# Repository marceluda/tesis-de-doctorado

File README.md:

# Material complementario de la Tesis de Doctorado de Marcelo Luda

En este sitio se publicará el material complementario. Se incluyen Scripts de programación, fuentes de los dibujos, etc.

## Trabajo de Tesis

El trabajo de tesis se puede acceder mediante la [biblioteca digital](https://bibliotecadigital.exactas.uba.ar/) de la [Facultad de Ciencias Exactas y Naturales de la UBA](https://exactas.uba.ar/):

  * Registro: https://bibliotecadigital.exactas.uba.ar/collection/tesis/document/tesis_n7160_Luda
  * [BAJAR PDF](https://bibliotecadigital.exactas.uba.ar/download/tesis/tesis_n7160_Luda.pdf)

## Material disponible en este repositorio

 - [Capítulo 6: Estructura atómica del Rubidio](https://github.com/marceluda/tesis-de-doctorado/tree/main/cap06)
 - [Capítulo 7: Modelo de espectroscopía de absorción](https://github.com/marceluda/tesis-de-doctorado/tree/main/cap07)
 - [Capítulo 8: Modelo de atrapamiento coherente de población (CPT)](https://github.com/marceluda/tesis-de-doctorado/tree/main/cap08)
 - [Capítulo 9: Espectroscopía de absorción de gas de Rb usando un microcontrolador Arduino](https://github.com/marceluda/tesis-de-doctorado/tree/main/cap09)
 - [Capítulo 15: Estabilización de λ a Fabry-Perot mediante PDH](https://github.com/marceluda/tesis-de-doctorado/tree/main/cap15)
 - [Capítulo 18: Espectro de absorción y control de λ](https://github.com/marceluda/tesis-de-doctorado/tree/main/cap18)
 - [Capítulo 19: Espectro de CPT y control de RF](https://github.com/marceluda/tesis-de-doctorado/tree/main/cap19)

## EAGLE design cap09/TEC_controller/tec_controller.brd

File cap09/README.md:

# Capítulo 9: Espectroscopía de absorción de gas de Rb usando un microcontrolador Arduino

Se montó un sistema de actuadores para controlar un ECDL y realizar un experimento de espectroscopía de absorción saturada, como en este esquema:

Se implementó un algoritmo de estabilización a un pozo de transmitancia, adquiriendo porciones del espectro en el entorno de longitud de onda del láser, realizando un ajuste lineal y corrigiendo la en función del valor de la pendiente. Aquí se puede ver una animación del programa en funcionamiento:

Para ello se debió controlar:
  - Corriente del láser
  - Temperatura del láser
  - Posición de la red de difracción, emdiante una tensión en un PZT

Se desarrollaron circuitos controladores para cada una de estas variables físicas. También se desarrolló un sistema de instrumentación basado en Arduino que funcionó como un comando central de operación.

## Controladores

### Controlador de PZT

Simplemente es un circuito de adaptación para el integrado [E-661.OE](hojas_de_datos/e-660_userpz45e223.pdf). Tiene un canal de control de off-set y otro de barrido.
El de off-set puede ser controlado por una entrada PWM  o mediante un potenciómetro multivuelta.
El de barrido por una entrada BNC o por otro PWM. Los canale se configuran mediante dos jumpres.

-------

<p align="center">
<strong>
<a href="DriverPZT">Driver PZT</a>
</strong>
</p>

-------

### Controlador de Corriente

Es un circuito de adaptación de tensiones para controlar el integrado [FL500](hojas_de_datos/fl500.pdf), que es una fuente de corriente de hasta 500 mA.
Tiene un control de off-set t un control de barrido, que incluye atenuación variable y la posibilidad de invertir la dirección de barrido respecto a la señal de control de entrada.

-------

<p align="center">
<strong>
<a href="DriverFL500">Driver Corriente</a>
</strong>
</p>

-------

### Controlador de Temperatura

Es un circuito de realimentación negativa con un controlador PID para estabilizar la temperatura del láser. Actúa sobre una celda Peltier y sensa un terminstor, que es comparado con una tensión de referencia.

-------

<p align="center">
<strong>
<a href="TEC_controller">Driver TEC</a>
</strong>
</p>

-------

## Controlador central basado en Arduino

Es un *shield* para [Arduino MEGA 2560](https://store.arduino.cc/usa/mega-2560-r3) que permite incorporarle:

  * Generador de barridos triangulares que incluye:
    * Control de frecuencia
    * Control de amplitud de barrido
    * Control de off-set
  * ADC con amplificación y offset
  * DACs a base de PWM y pasabajos

### Diseño de circuito

-------

<p align="center">
<strong>
<a href="shield-control">Arduino Shield-Control</a>
</strong>
</p>

-------

### Centro de comandos

Se programó el dispositivo para correr un [centro de comandos](command_center) con comunicación serie para controlar el comportamiento del controlador, configurar parámetros y adquirir datos.

```graphql
# Los comandos se componen de la siguiente estructura:
# (comando)( )(param1)[ ][param2]
# donde () implica obligatorio, [] opcional y ( ) es un white_space

# debug modes
# 0   --> nada de debug
# >=5 --> info irrelevante

Comandos

get -----> P(2-13)  ---> Trae ultimo valor seteado al pin Px
      |--> D(24-29) ---> Lee valor digital del pin Dx
      |--> D(30-39) ---> Trae ultimo valor seteado al pin Dx
      |--> A(0-4)   ---> Lee valor analogico del pin Ax (pin x+54)

set -----> P(2-13) (0-255) ---> Setea el PWM Px en un valor 0-255
      |--> D(30-39) (0-1)  ---> Setea el pin digital Dx en un valor 0-1

debug ---> (num)          ---> Setea el modo de debugging en el valor "num"

trig ---> (off||up||down) ---> Habilita el trigger en el pin 19 para subida, bajada, o lo apaga

binary --> (num)          ---> Si num>0 habilita el modo binario. Sino, lo deshabilita.

vref ---> (num)   ---> Cambia la tensión de referencia del ADC
                          |--> num=1  ---> Vref=1.1V
                          |--> num=2  ---> Vref=2.56V
                          |--> num=9  ---> Vref externo
                          |--> cualquier otro ---> Vref=Vcc~5V (DEFAULT)

curv  ----> A(0-4)   ---> Levanta NN puntos del pin Ax

curv2 ----> A(0-4) ----> D(19-20||30-39)   ---> Levanta NN puntos del pin Ax y otra de NN puntos del pin Dx

# En modo binario las respuestas son:

--> 0 EOT                    ---> Comando recibido
--> 1 EOT Val EOT            ---> Envio de un integer binario
--> 2 EOT Num EOT Vals EOT   ---> Envio de Num integers binarios
--> 9 EOT msg EOT            ---> Envio de un texto informativo

```

<details>
<summary>Ejemplo de comando remoto en Matlab</summary>

```MATLAB

%s=serial('/dev/ttyACM1');
s=serial('COM6');
set(s,'BaudRate',57600);
set(s,'InputBufferSize',4096);

% Nota: para que el MATLAB lea correctamente el puerto es necesario
%       crear un archivo en el home folder donde abre el matlab
%       que en mi caso es /home/lolo
%
%       Archivo: java.opts
%       -Dgnu.io.rxtx.SerialPorts=/dev/ttyS0:/dev/ttyS1:/dev/USB0:/dev/ttyACM0:/dev/ttyACM1
%

fopen(s)
pause(2)
leer(s)

cmd(s,'binary 1')
cmd(s,'trig up')
cmd(s,'trig down')
cmd(s,'trig off')

leer(s)

escribir(s,'\n')

for i=1:20
    plot(cmd(s,'curv A0')*5/1024,'.-')
    pause(0.1)
end

escala=1024

cmd(s,'ate 15')
cmd(s,'set P9 115')

[yy,tt]=curvA0(s);
plot(tt,yy,'.-')
plot(tt,smooth(yy),'.-')

cmd(s,'vref 9')
cmd(s,'delay 250 u')

cmd(s,'set P10 150')
cmd(s,'set P10 0')
cmd(s,'set P9 100')

cmd(s,'set D30 0')
cmd(s,'set D32 0')
cmd(s,'set D34 0')
cmd(s,'set D36 1')

cmd(s,'vref 5')
cmd(s,'vref 1')

tic()
cmd(s,'curv2 A0 D26')
toc()

fclose(s)
```

</details>

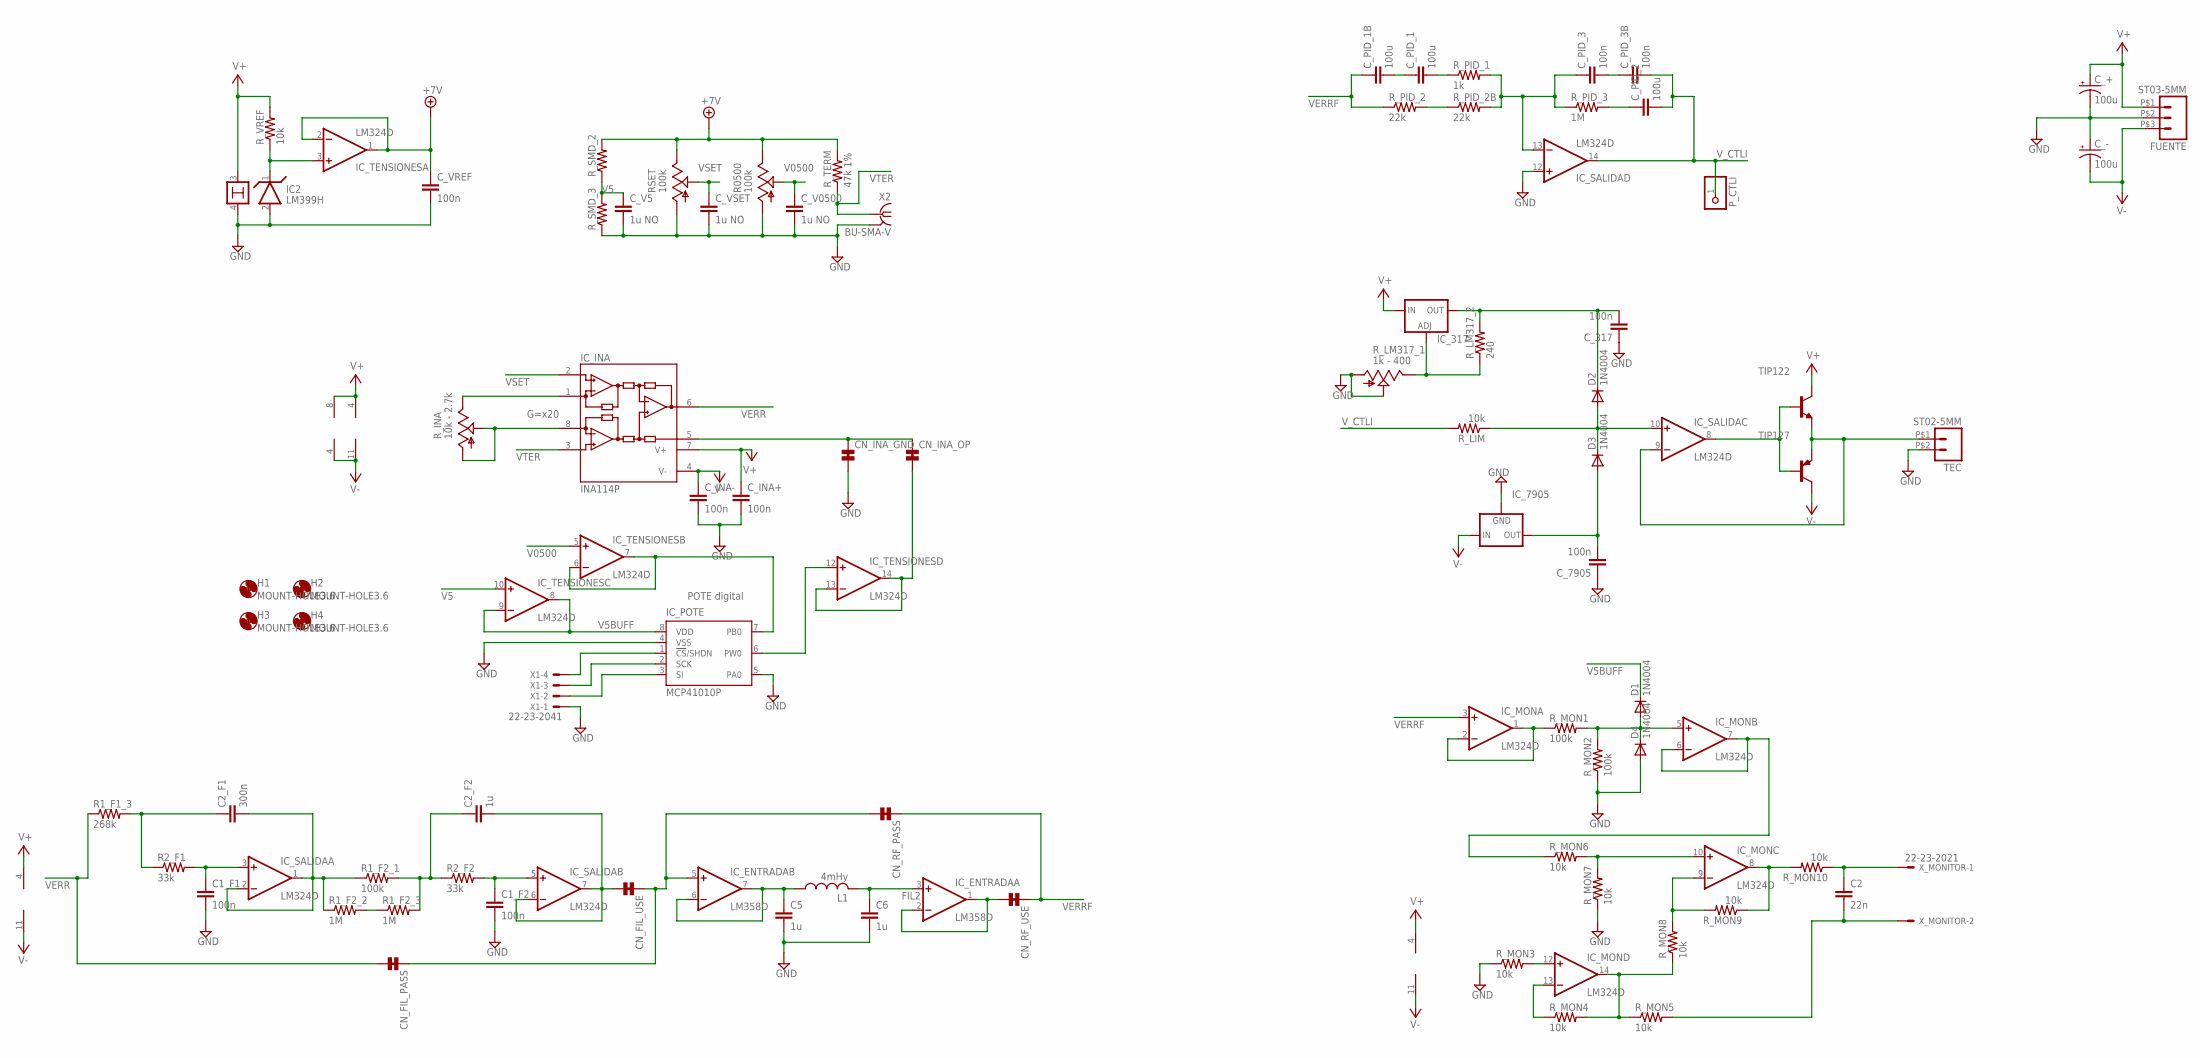
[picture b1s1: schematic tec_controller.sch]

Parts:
C1_F1, C1_F2: 100n; C0603
C2: 22n; C1206
C2_F1: 300n; C0603
C2_F2, C5, C6: 1u; C0805
CN_FIL_PASS: LINK; LINK_PAC_0603
CN_FIL_USE: LINK; LINK_PAC_0603
CN_INA_GND: LINK; LINK_PAC_0603
CN_INA_OP: LINK; LINK_PAC_0603
CN_RF_PASS: LINK; LINK_PAC_0603
CN_RF_USE: LINK; LINK_PAC_0603
C_317, C_7905: 100n; C0603
C_+: 100u; E3,5-10
C_-: 100u; E3,5-10
C_INA+: 100n; C0603
C_INA-: 100n; C0603
C_PID_1, C_PID_1B, C_PID_2: 100u; C050-050X075
C_PID_3, C_PID_3B: 100n; C0603
C_V5, C_V0500: 1u NO; C0805
C_VREF: 100n; C0603
C_VSET: 1u NO; C0805
D1, D2, D3, D4: 1N4004; DO41-10
FUENTE: ST03-5MM; EK500V-03P
H1, H2, H3, H4: MOUNT-HOLE3.6; 3,6
IC2: LM399H; TO39/4
IC_317: LM317TS; 317TS
IC_7905: 79XXS
IC_ENTRADA: LM358D; SO08
IC_INA: INA114P; DIL08
IC_MON: LM324D; SO14
IC_POTE: MCP41010P; DIL8
IC_SALIDA: LM324D; SO14
IC_TENSIONES: LM324D; SO14
L1: 4mHy; 0207/15
P_CTLI: PINHD-1X1; 1X01
R1_F1_3: 268k; 0207/15
R1_F2_1: 100k; M1206
R1_F2_2, R1_F2_3: 1M; M1206
R2_F1, R2_F2: 33k; M1206
R0500: 100k; B64Y
RSET: 100k; B64Y
R_INA: 10k - 2.7k; B64Y
R_LIM: 10k; M1206
R_LM317_1: 1k - 400; B64Y
R_LM317_2: 240; 0207/10
R_MON1, R_MON2: 100k; M1206
R_MON3, R_MON4, R_MON5, R_MON6, R_MON7, R_MON8, R_MON9, R_MON10: 10k; M1206
R_PID_1: 1k; M1206
R_PID_2, R_PID_2B: 22k; M1206
R_PID_3: 1M; M1206
R_SMD_2, R_SMD_3: R-US_M1206; M1206
R_TERM: 47k 1%; 0207/10
R_VREF: 10k; M1206
TEC: ST02-5MM; EK500V-02P
TIP122: -NPN-TO126V; TO126V
TIP127: -PNP-TO126V; TO126V
X1: 22-23-2041
X2: BU-SMA-V
X_MONITOR: 22-23-2021

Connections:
+7V: C_VREF.1, IC_TENSIONES.1 (OUT), IC_TENSIONES.2 (-IN), R0500.E, RSET.E, R_SMD_2.2, R_TERM.2
FIL2: C6.1, IC_ENTRADA.3 (+IN), L1.2
GND: C1_F1.2, C1_F2.2, C5.2, C6.2, CN_INA_GND.2, C_317.1, C_7905.1, C_+.-, C_-.+, C_INA+.2, C_INA-.2, C_V5.2, C_V0500.2, C_VREF.2, C_VSET.2, D4.A, FUENTE.P$2 (2), IC2.2, IC2.4, IC_7905.GND, IC_POTE.4 (VSS), IC_POTE.5 (PA0), IC_SALIDA.12 (+IN), R0500.A, RSET.A, R_LM317_1.A, R_LM317_1.S, R_MON2.1, R_MON3.1, R_MON7.1, R_SMD_3.1, TEC.P$2 (2), X1.1, X2.2, X2.3 (2), X2.4 (2), X2.5 (2)
unnamed: IC2.1, IC_TENSIONES.3 (+IN), R_VREF.1
unnamed: IC_INA.1 (RG), R_INA.E
unnamed: IC_INA.8 (RG), R_INA.A, R_INA.S
unnamed: C_PID_1.2, R_PID_1.1
unnamed: IC_MON.1 (OUT), IC_MON.2 (-IN), R_MON1.1
unnamed: IC_MON.12 (+IN), R_MON3.2
unnamed: C5.1, IC_ENTRADA.6 (-IN), IC_ENTRADA.7 (OUT), L1.1
unnamed: CN_RF_USE.2, IC_ENTRADA.1 (OUT), IC_ENTRADA.2 (-IN)
unnamed: C2_F1.1, R1_F1_3.2, R2_F1.1
unnamed: C1_F1.1, IC_SALIDA.3 (+IN), R2_F1.2
unnamed: C2_F1.2, IC_SALIDA.1 (OUT), IC_SALIDA.2 (-IN), R1_F2_1.1, R1_F2_2.1
unnamed: R1_F2_2.2, R1_F2_3.1
unnamed: C2_F2.1, R1_F2_1.2, R1_F2_3.2, R2_F2.1
unnamed: IC_POTE.7 (PB0), IC_TENSIONES.6 (-IN), IC_TENSIONES.7 (OUT)
unnamed: C1_F2.1, IC_SALIDA.5 (+IN), R2_F2.2
unnamed: IC_POTE.6 (PW0), IC_TENSIONES.12 (+IN)
unnamed: CN_INA_GND.1, CN_INA_OP.1, IC_INA.5 (REF)
unnamed: IC_POTE.1 (!CS!/SHDN), X1.4
unnamed: CN_INA_OP.2, IC_TENSIONES.13 (-IN), IC_TENSIONES.14 (OUT)
unnamed: IC_POTE.2 (SCK), X1.3
unnamed: IC_POTE.3 (SI), X1.2
unnamed: R_PID_2.2, R_PID_2B.1
unnamed: C_PID_1.1, C_PID_1B.2
unnamed: C_PID_3.1, IC_SALIDA.13 (-IN), R_PID_1.2, R_PID_2B.2, R_PID_3.1
unnamed: IC_317.1 (ADJ), R_LM317_1.E, R_LM317_2.1
unnamed: C_PID_2.1, R_PID_3.2
unnamed: D2.A, D3.C, IC_SALIDA.10 (+IN), R_LIM.1
unnamed: C_PID_3.2, C_PID_3B.1
unnamed: IC_SALIDA.8 (OUT), TIP122.3 (B), TIP127.3 (B)
unnamed: D1.A, D4.C, IC_MON.5 (+IN), R_MON1.2, R_MON2.2
unnamed: IC_MON.6 (-IN), IC_MON.7 (OUT), R_MON6.1
unnamed: IC_MON.10 (+IN), R_MON6.2, R_MON7.2
unnamed: IC_MON.9 (-IN), R_MON8.2, R_MON9.2
unnamed: IC_MON.14 (OUT), R_MON4.2, R_MON5.1, R_MON8.1
unnamed: IC_MON.13 (-IN), R_MON4.1
unnamed: C2.2, R_MON5.2, X_MONITOR.2
unnamed: IC_MON.8 (OUT), R_MON9.1, R_MON10.2
unnamed: C2.1, R_MON10.1, X_MONITOR.1
V5: C_V5.1, IC_TENSIONES.10 (+IN), R_SMD_2.1, R_SMD_3.2
V5BUFF: D1.C, IC_POTE.8 (VDD), IC_TENSIONES.8 (OUT), IC_TENSIONES.9 (-IN)
V0500: C_V0500.1, IC_TENSIONES.5 (+IN), R0500.S
V+: C_+.+, C_INA+.1, FUENTE.P$1 (1), IC2.3, IC_317.3 (IN), IC_ENTRADA.8 (V+), IC_INA.7 (V+), IC_MON.4 (V+), IC_SALIDA.4 (V+), IC_TENSIONES.4 (V+), R_VREF.2, TIP122.2 (C)
V-: C_-.-, C_INA-.1, FUENTE.P$3 (3), IC_7905.IN, IC_ENTRADA.4 (V-), IC_INA.4 (V-), IC_MON.11 (V-), IC_SALIDA.11 (V-), IC_TENSIONES.11 (V-), TIP127.2 (C)
VERR: CN_FIL_PASS.2, IC_INA.6 (OUT), R1_F1_3.1
VERRF: CN_RF_PASS.1, CN_RF_USE.1, C_PID_1B.1, IC_MON.3 (+IN), R_PID_2.1
VERRF_B: CN_FIL_PASS.1, CN_FIL_USE.1, CN_RF_PASS.2, IC_ENTRADA.5 (+IN)
VERRF_SALIDA: C2_F2.2, CN_FIL_USE.2, IC_SALIDA.6 (-IN), IC_SALIDA.7 (OUT)
VSET: C_VSET.1, IC_INA.2 (-IN), RSET.S
VTEC: IC_SALIDA.9 (-IN), TEC.P$1 (1), TIP122.1 (E), TIP127.1 (E)
VTER: IC_INA.3 (+IN), R_TERM.1, X2.1
V_317: C_317.2, D2.C, IC_317.2 (OUT), R_LM317_2.2
V_7905: C_7905.2, D3.A, IC_7905.OUT
V_CTLI: C_PID_2.2, C_PID_3B.2, IC_SALIDA.14 (OUT), P_CTLI.1, R_LIM.2

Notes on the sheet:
POTE digital
G=x20

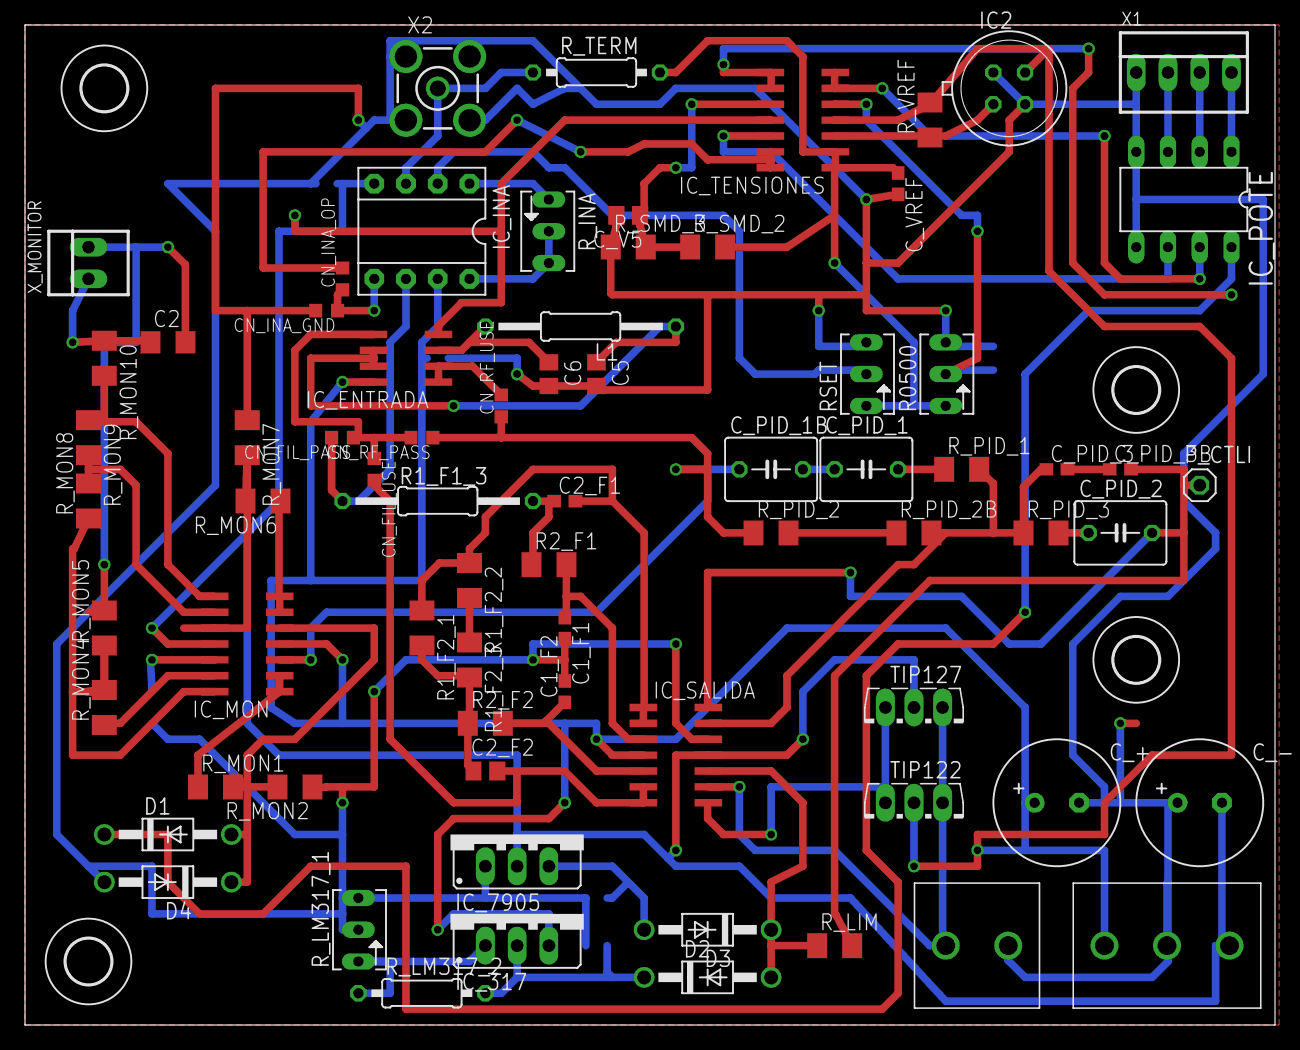
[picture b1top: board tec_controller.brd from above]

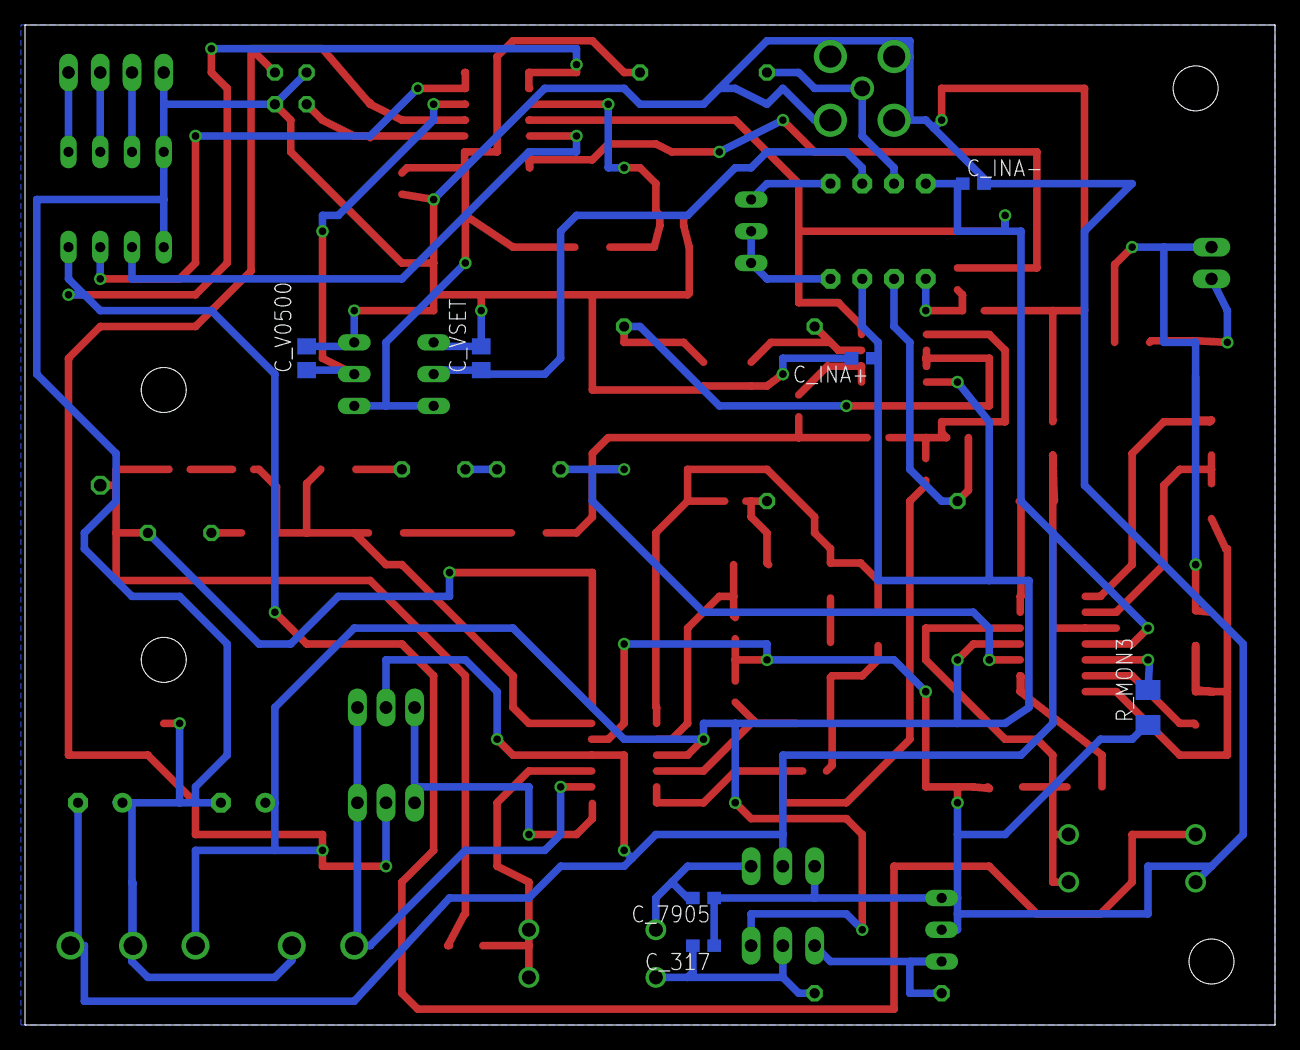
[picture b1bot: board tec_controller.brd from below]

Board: 2 copper layers, 100.0 x 80.0 mm, 84 parts (7 on the bottom side), 56 nets.

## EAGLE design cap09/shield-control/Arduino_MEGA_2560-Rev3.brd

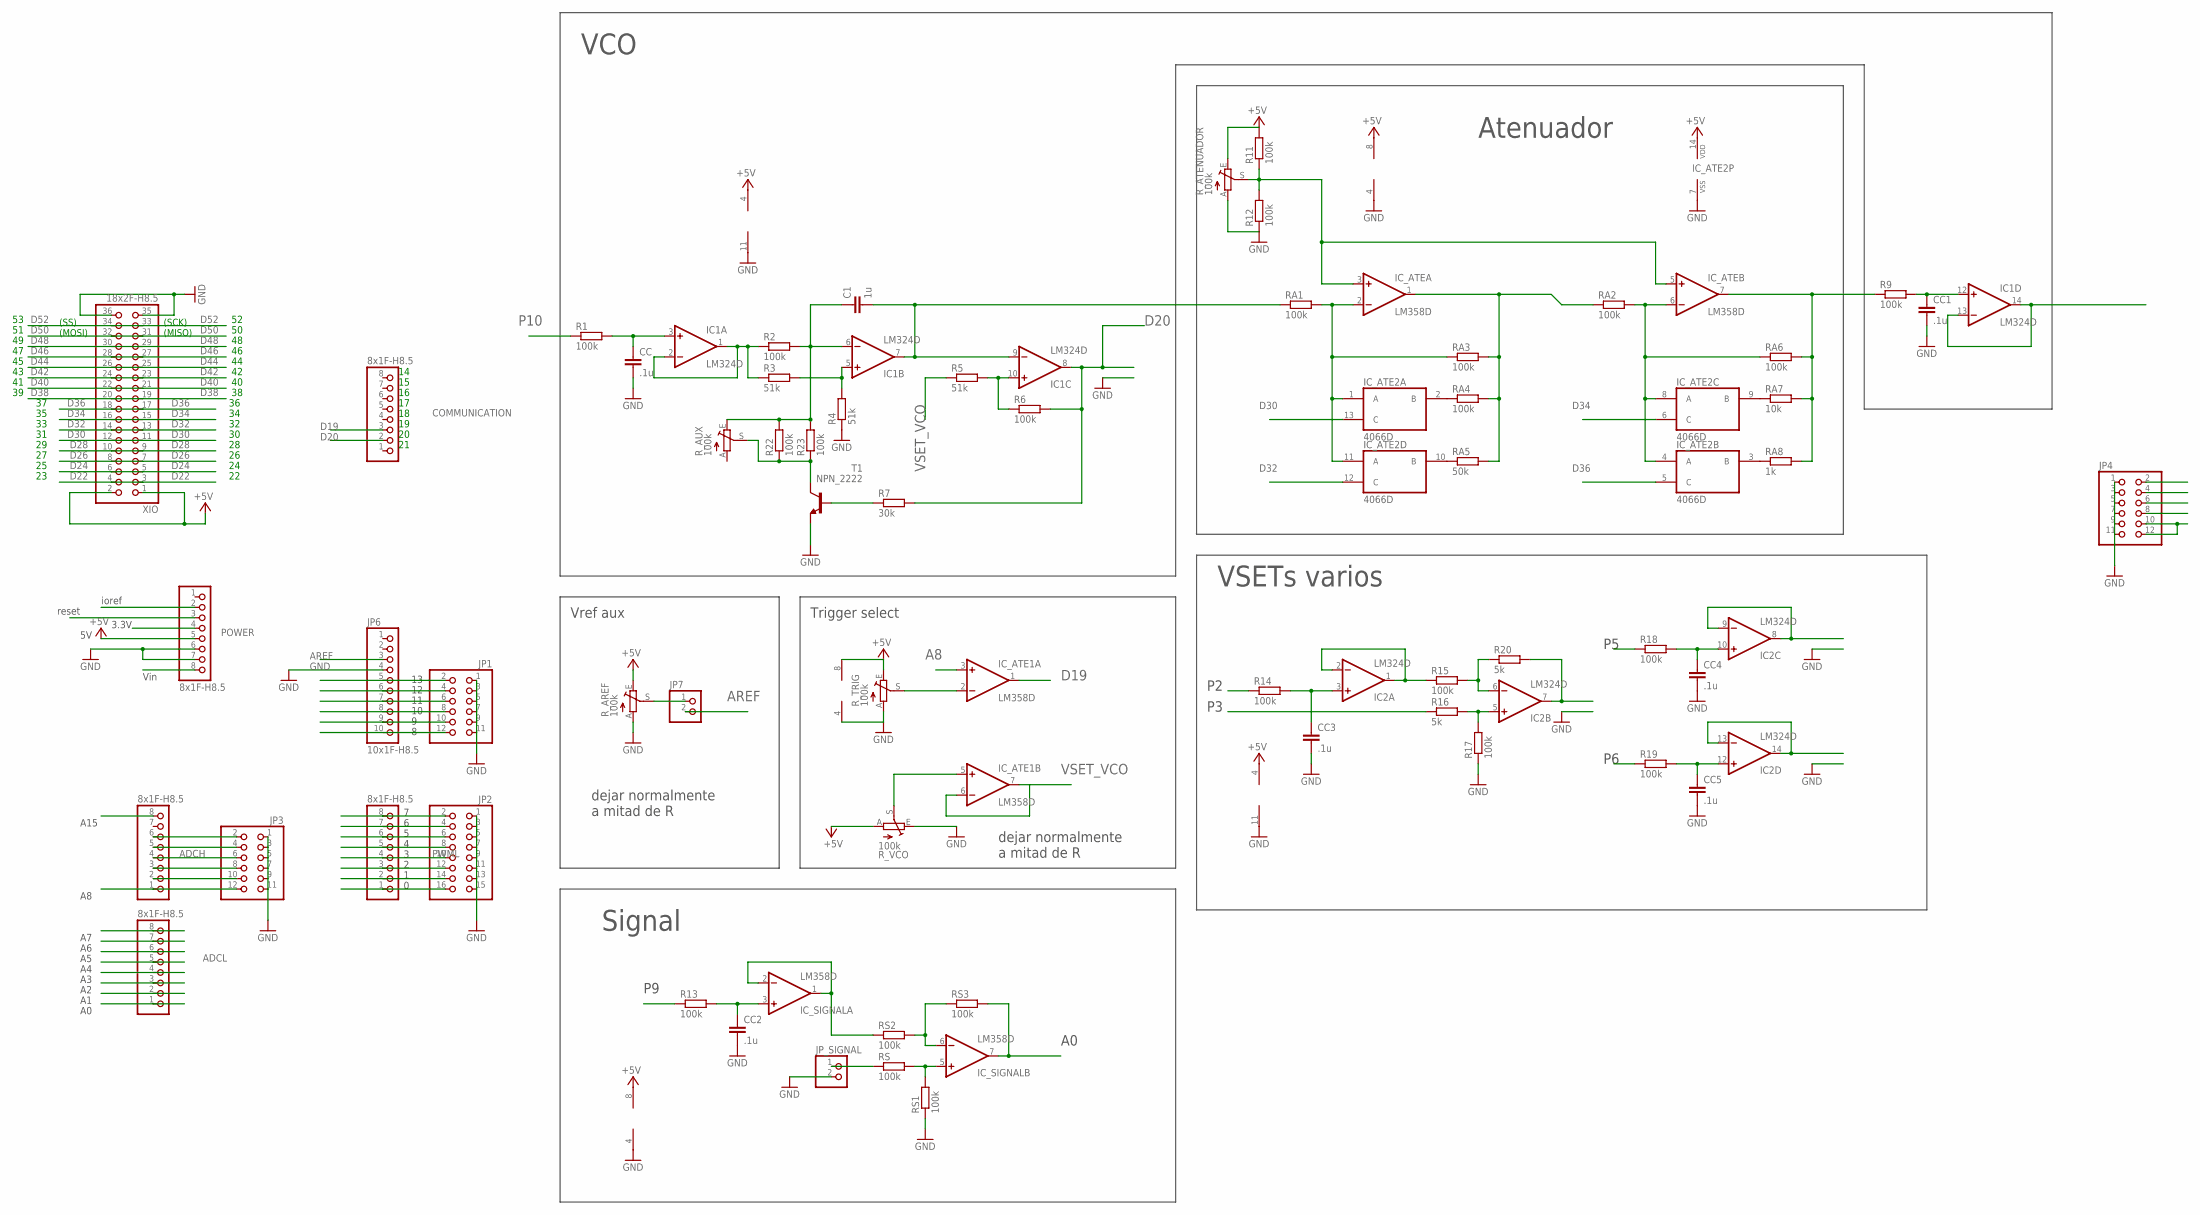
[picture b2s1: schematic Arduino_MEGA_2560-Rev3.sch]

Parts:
ADCH: 8x1F-H8.5; 1X08
ADCL: 8x1F-H8.5; 1X08
C1: 1u; C1812
CC, CC1, CC2, CC3, CC4, CC5: .1u; C1812
COMMUNICATION: 8x1F-H8.5; 1X08
IC1, IC2: LM324D; SO14
IC_ATE, IC_ATE1: LM358D; SO08
IC_ATE2: 4066D; SO14
IC_SIGNAL: LM358D; SO08
JP1, JP3, JP4: PINHD-2X6; 2X06
JP2: PINHD-2X8; 2X08
JP6: 10x1F-H8.5; 1X10
JP7: PINHD-1X2; 1X02
JP_SIGNAL: PINHD-1X2; 1X02
POWER: 8x1F-H8.5; 1X08
PWML: 8x1F-H8.5; 1X08
R1, R2, R6, R9, R11, R12, R13, R14, R15, R17, R18, R19, R22, R23: 100k; R1206
R3, R4, R5: 51k; R1206
R7: 30k; 0204/7
R16, R20: 5k; R1206
RA1, RA2, RA3, RA4, RA6: 100k; R1206
RA5: 50k; R1206
RA7: 10k; 0204/7
RA8: 1k; 0204/7
RS, RS1, RS2, RS3: 100k; R1206
R_AREF: 100k; B64Y
R_ATENUADOR: 100k; B64Y
R_AUX: 100k; B64Y
R_TRIG: 100k; B64Y
R_VCO: 100k; B64Y
T1: NPN_2222; TO19_SUP
XIO: 18x2F-H8.5; 2X18

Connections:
3V3: POWER.4
+5V: IC1.4 (V+), IC2.4 (V+), IC_ATE.8 (V+), IC_ATE1.8 (V+), IC_ATE2.14 (VDD), IC_SIGNAL.8 (V+), POWER.5, R11.2, R_AREF.E, R_ATENUADOR.E, R_TRIG.E, R_VCO.A, XIO.1, XIO.2
A0: ADCL.1, IC_SIGNAL.7 (OUT), RS3.2
A1: ADCL.2
A2: ADCL.3
A3: ADCL.4
A4: ADCL.5
A5: ADCL.6
A6: ADCL.7
A7: ADCL.8
A8: ADCH.1, IC_ATE1.3 (+IN), JP3.12
A9: ADCH.2, JP3.10
A9BIS: IC_ATE1.5 (+IN), R_VCO.S
A10: ADCH.3, JP3.8
A11: ADCH.4, JP3.6
A12: ADCH.5, JP3.4
A13: ADCH.6, JP3.2
A15: ADCH.8
AREF: JP6.3, JP7.2
D19: COMMUNICATION.3, IC_ATE1.1 (OUT)
D20: COMMUNICATION.2, IC1.8 (OUT), JP4.2, R6.2, R7.2
D22: XIO.3, XIO.4
D24: XIO.5, XIO.6
D26: XIO.7, XIO.8
D28: XIO.9, XIO.10
D30: IC_ATE2.13 (C), XIO.11, XIO.12
D32: IC_ATE2.12 (C), XIO.13, XIO.14
D34: IC_ATE2.6 (C), XIO.15, XIO.16
D36: IC_ATE2.5 (C), XIO.17, XIO.18
D38: XIO.19, XIO.20
D40: XIO.21, XIO.22
D42: XIO.23, XIO.24
D44: XIO.25, XIO.26
D46: XIO.27, XIO.28
D48: XIO.29, XIO.30
D50: XIO.31, XIO.32
D52: XIO.33, XIO.34
GND: CC.2, CC1.2, CC2.2, CC3.2, CC4.2, CC5.2, IC1.11 (V-), IC2.11 (V-), IC_ATE.4 (V-), IC_ATE1.4 (V-), IC_ATE2.7 (VSS), IC_SIGNAL.4 (V-), JP1.1, JP1.3, JP1.5, JP1.7, JP1.9, JP1.11, JP2.1, JP2.3, JP2.5, JP2.7, JP2.9, JP2.11, JP2.13, JP2.15, JP3.1, JP3.3, JP3.5, JP3.7, JP3.9, JP3.11, JP4.1, JP4.3, JP4.5, JP4.7, JP4.9, JP4.11, JP6.4, JP_SIGNAL.2, POWER.6, POWER.7, R4.1, R12.1, R17.1, RS1.1, R_AREF.A, R_ATENUADOR.A, R_TRIG.A, R_VCO.E, T1.3 (E), XIO.35, XIO.36
unnamed: IC_ATE1.2 (-IN), R_TRIG.S
unnamed: CC.1, IC1.3 (+IN), R1.2
unnamed: IC1.1 (OUT), IC1.2 (-IN), R2.1, R3.1
unnamed: IC_ATE.2 (-IN), IC_ATE2.1 (A), IC_ATE2.11 (A), RA1.2, RA3.1
unnamed: C1.1, IC1.6 (-IN), R2.2, R22.2, R23.2, R_AUX.E
unnamed: IC_ATE2.3 (B), RA8.1
unnamed: IC1.5 (+IN), R3.2, R4.2
unnamed: IC1.10 (+IN), R5.2, R6.1
unnamed: IC_ATE2.10 (B), RA5.1
unnamed: R7.1, T1.2 (B)
unnamed: CC1.1, IC1.12 (+IN), R9.2
unnamed: IC_SIGNAL.1 (OUT), IC_SIGNAL.2 (-IN), RS2.1
unnamed: IC_ATE.6 (-IN), IC_ATE2.4 (A), IC_ATE2.8 (A), RA2.2, RA6.1
unnamed: IC_ATE.1 (OUT), RA2.1, RA3.2, RA4.2, RA5.2
unnamed: IC_ATE2.2 (B), RA4.1
unnamed: IC_SIGNAL.5 (+IN), RS.2, RS1.2
unnamed: IC_SIGNAL.6 (-IN), RS2.2, RS3.1
unnamed: CC3.1, IC2.3 (+IN), R14.2
unnamed: IC_ATE2.9 (B), RA7.1
unnamed: IC2.1 (OUT), IC2.2 (-IN), R15.1
unnamed: CC2.1, IC_SIGNAL.3 (+IN), R13.2
unnamed: IC2.6 (-IN), R15.2, R20.1
unnamed: IC_ATE.7 (OUT), R9.1, RA6.2, RA7.2, RA8.2
unnamed: IC_ATE.3 (+IN), IC_ATE.5 (+IN), R11.1, R12.2, R_ATENUADOR.S
unnamed: IC2.5 (+IN), R16.2, R17.2
unnamed: CC5.1, IC2.12 (+IN), R19.2
unnamed: CC4.1, IC2.10 (+IN), R18.2
unnamed: R22.1, R23.1, R_AUX.S, T1.1 (C)
unnamed: JP7.1, R_AREF.S
P0: JP2.16, PWML.1
P1: JP2.14, PWML.2
P2: JP2.12, PWML.3, R14.1
P3: JP2.10, PWML.4, R16.1
P4: JP2.8, PWML.5
P5: JP2.6, PWML.6, R18.1
P6: JP2.4, PWML.7, R19.1
P7: JP2.2, PWML.8
P8: JP1.12, JP6.10
P9: JP1.10, JP6.9, R13.1
P10: JP1.8, JP6.8, R1.1
P11: JP1.6, JP6.7
P12: JP1.4, JP6.6
P13: JP1.2, JP6.5
SIGNAL: JP_SIGNAL.1, RS.1
SP5: IC2.8 (OUT), IC2.9 (-IN), JP4.4
SP6: IC2.13 (-IN), IC2.14 (OUT), JP4.6
SPSUPER: IC2.7 (OUT), JP4.8, R20.2
TRIANGULAR: C1.2, IC1.7 (OUT), IC1.9 (-IN), RA1.1
TRIANG_ATE: IC1.13 (-IN), IC1.14 (OUT), JP4.10, JP4.12
VIN: POWER.8
VSET_VCO: IC_ATE1.6 (-IN), IC_ATE1.7 (OUT), R5.1

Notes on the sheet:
(SS)
(MOSI)
(SCK)
(MISO)
Vin
3.3V
reset
ioref
A15
VCO
Atenuador
Signal
Vref aux
Trigger select
dejar normalmente a mitad de R
VSETs varios

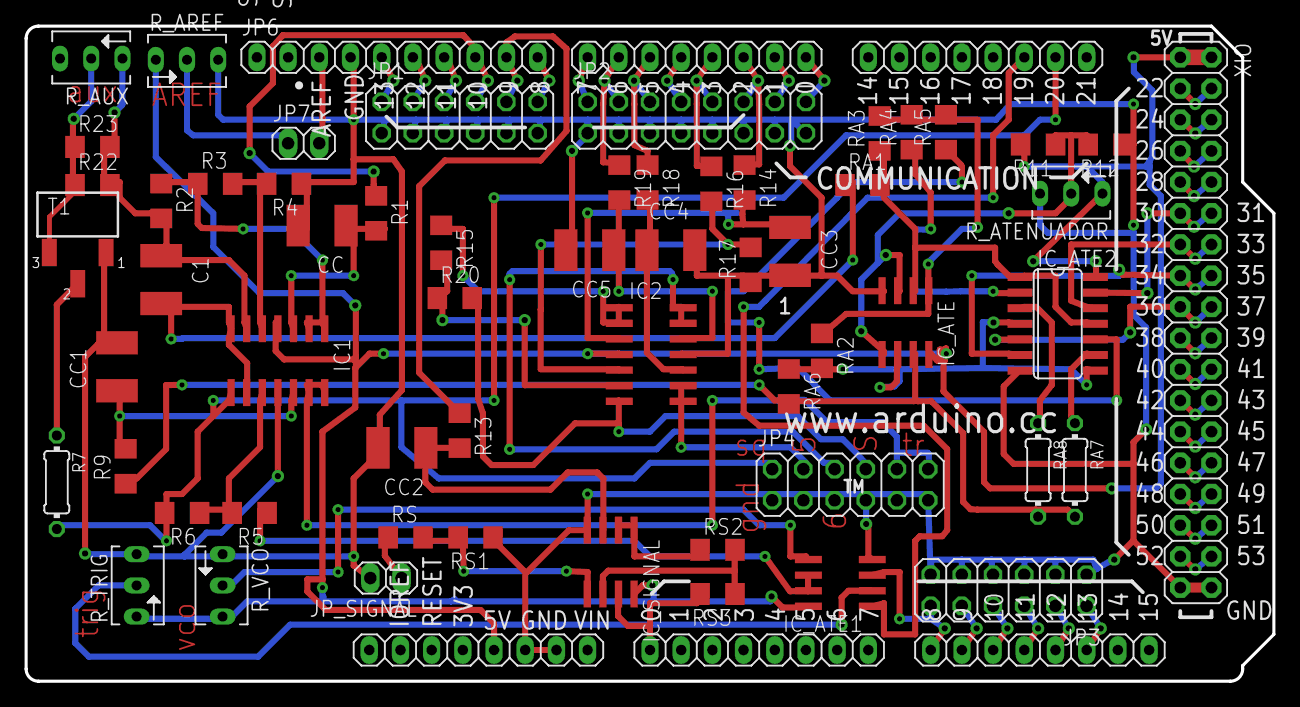
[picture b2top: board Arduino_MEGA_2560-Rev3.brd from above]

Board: 2 copper layers, 101.6 x 53.3 mm, 64 parts (0 on the bottom side), 79 nets.

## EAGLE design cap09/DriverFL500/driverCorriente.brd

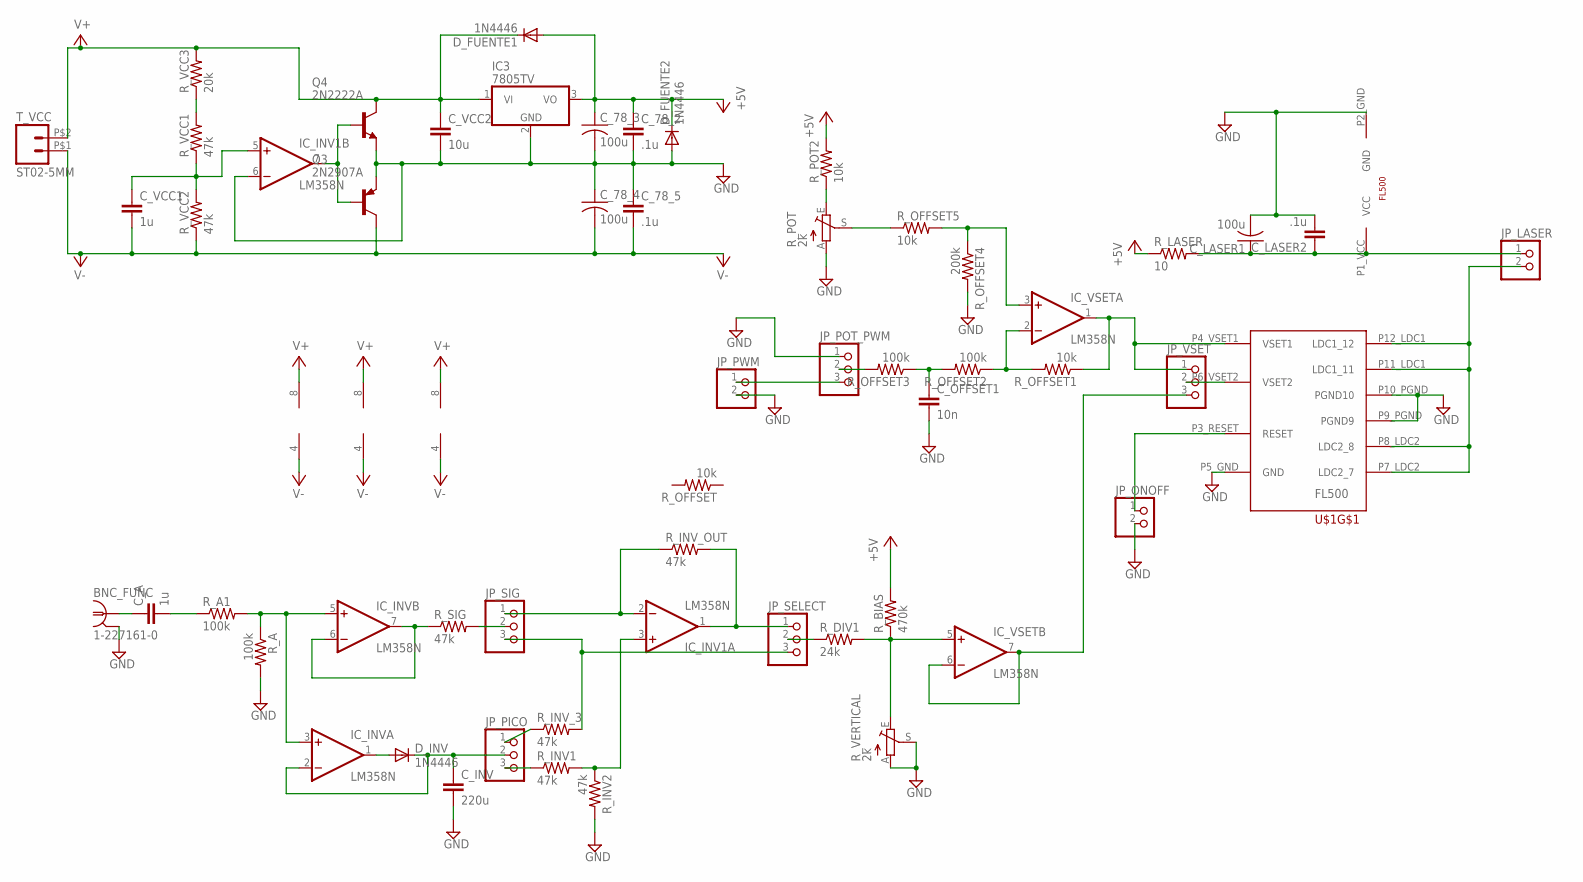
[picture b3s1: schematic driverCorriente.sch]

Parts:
BNC_FUNC: 1-227161-0; AMP_227161
C_78_2, C_78_5: .1u; C050-045X075
C_78_3, C_78_4: 100u; C050-075X075
C_A: 1u; C050-045X075
C_INV: 220u; C050-045X075
C_LASER1: 100u; C050-075X075
C_LASER2: .1u; C050-045X075
C_OFFSET1: 10n; C050-045X075
C_VCC1: 1u; C050-045X075
C_VCC2: 10u; C050-045X075
D_FUENTE1, D_FUENTE2: 1N4446; DO35-10
D_INV: 1N4446; DO35-10
IC3: 7805TV; TO220V
IC_INV, IC_INV1: LM358N; DIL08
IC_VSET: LM358N; DIL08
JP_LASER: PINHD-1X2; 1X02
JP_ONOFF: PINHD-1X2; 1X02
JP_PICO: PINHD-1X3; 1X03
JP_POT_PWM: PINHD-1X3; 1X03
JP_PWM: PINHD-1X2; 1X02
JP_SELECT: PINHD-1X3; 1X03
JP_SIG: PINHD-1X3; 1X03
JP_VSET: PINHD-1X3; 1X03
Q3: 2N2907A; TO18
Q4: 2N2222A; TO18
R_A, R_A1: 100k; 0207/12
R_BIAS: 470k; 0207/12
R_DIV1: 24k; 0207/12
R_INV1, R_INV2: 47k; 0207/12
R_INV_3: 47k; 0207/12
R_INV_OUT: 47k; 0207/12
R_LASER: 10; 0207/12
R_OFFSET, R_OFFSET1, R_OFFSET5: 10k; 0207/12
R_OFFSET2, R_OFFSET3: 100k; 0207/12
R_OFFSET4: 200k; 0207/12
R_POT: 2k; B64Y
R_POT2: 10k; 0207/12
R_SIG: 47k; 0207/12
R_VCC1, R_VCC2: 47k; 0207/12
R_VCC3: 20k; 0207/12
R_VERTICAL: 2k; B64Y
T_VCC: ST02-5MM; EK500V-02P
U$1: FL500

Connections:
+5V: C_78_2.1, C_78_3.1, D_FUENTE1.A, D_FUENTE2.C, IC3.3 (VO), R_BIAS.2, R_LASER.1, R_POT2.2
GND: BNC_FUNC.2, C_78_2.2, C_78_3.2, C_78_4.1, C_78_5.1, C_INV.2, C_LASER1.2, C_LASER2.2, C_OFFSET1.2, C_VCC2.2, D_FUENTE2.A, IC3.2 (GND), IC_INV1.6 (-IN), JP_ONOFF.2, JP_POT_PWM.1, JP_PWM.2, Q3.1 (E), Q4.1 (E), R_A.2, R_INV2.2, R_OFFSET4.2, R_POT.A, R_VERTICAL.A, R_VERTICAL.S, U$1.P2_GND (GND), U$1.P5_GND (GND), U$1.P9_PGND (PGND9), U$1.P10_PGND (PGND10)
unnamed: JP_LASER.2, U$1.P7_LDC2 (LDC2_7), U$1.P8_LDC2 (LDC2_8), U$1.P11_LDC1 (LDC1_11), U$1.P12_LDC1 (LDC1_12)
unnamed: R_POT.E, R_POT2.1
unnamed: IC_VSET.1 (OUT), JP_VSET.1, R_OFFSET1.1, U$1.P4_VSET1 (VSET1)
unnamed: JP_ONOFF.1, U$1.P3_RESET (RESET)
unnamed: IC_INV.3 (+IN), IC_INV.5 (+IN), R_A.1, R_A1.2
unnamed: D_INV.A, IC_INV.1 (OUT)
unnamed: C_INV.1, D_INV.C, IC_INV.2 (-IN), JP_PICO.2
unnamed: JP_PICO.1, R_INV_3.1
unnamed: JP_SIG.2, R_SIG.2
unnamed: JP_SELECT.3, JP_SIG.3, R_INV_3.2
unnamed: JP_PICO.3, R_INV1.1
unnamed: IC_INV1.3 (+IN), R_INV1.2, R_INV2.1
unnamed: IC_INV1.2 (-IN), JP_SIG.1, R_INV_OUT.1
unnamed: IC_INV1.1 (OUT), JP_SELECT.1, R_INV_OUT.2
unnamed: JP_SELECT.2, R_DIV1.1
unnamed: IC_VSET.5 (+IN), R_BIAS.1, R_DIV1.2, R_VERTICAL.E
unnamed: IC_VSET.6 (-IN), IC_VSET.7 (OUT), JP_VSET.3
unnamed: BNC_FUNC.1, C_A.1
unnamed: JP_POT_PWM.2, R_OFFSET3.2
unnamed: JP_POT_PWM.3, JP_PWM.1
unnamed: JP_VSET.2, U$1.P6_VSET2 (VSET2)
unnamed: IC_INV.6 (-IN), IC_INV.7 (OUT), R_SIG.1
unnamed: C_A.2, R_A1.1
unnamed: C_VCC1.1, IC_INV1.5 (+IN), R_VCC1.1, R_VCC2.2
unnamed: R_VCC1.2, R_VCC3.1
unnamed: IC_INV1.7 (OUT), Q3.2 (B), Q4.2 (B)
unnamed: R_OFFSET5.1, R_POT.S
unnamed: IC_VSET.2 (-IN), R_OFFSET1.2, R_OFFSET2.1
unnamed: C_OFFSET1.1, R_OFFSET2.2, R_OFFSET3.1
unnamed: IC_VSET.3 (+IN), R_OFFSET4.1, R_OFFSET5.2
V+: C_VCC2.1, D_FUENTE1.C, IC3.1 (VI), IC_INV.8 (V+), IC_INV1.8 (V+), IC_VSET.8 (V+), Q4.3 (C), R_VCC3.2, T_VCC.P$2 (2)
V-: C_78_4.2, C_78_5.2, C_VCC1.2, IC_INV.4 (V-), IC_INV1.4 (V-), IC_VSET.4 (V-), Q3.3 (C), R_VCC2.1, T_VCC.P$1 (1)
VCC_LASER: C_LASER1.1, C_LASER2.1, JP_LASER.1, R_LASER.2, U$1.P1_VCC (VCC)

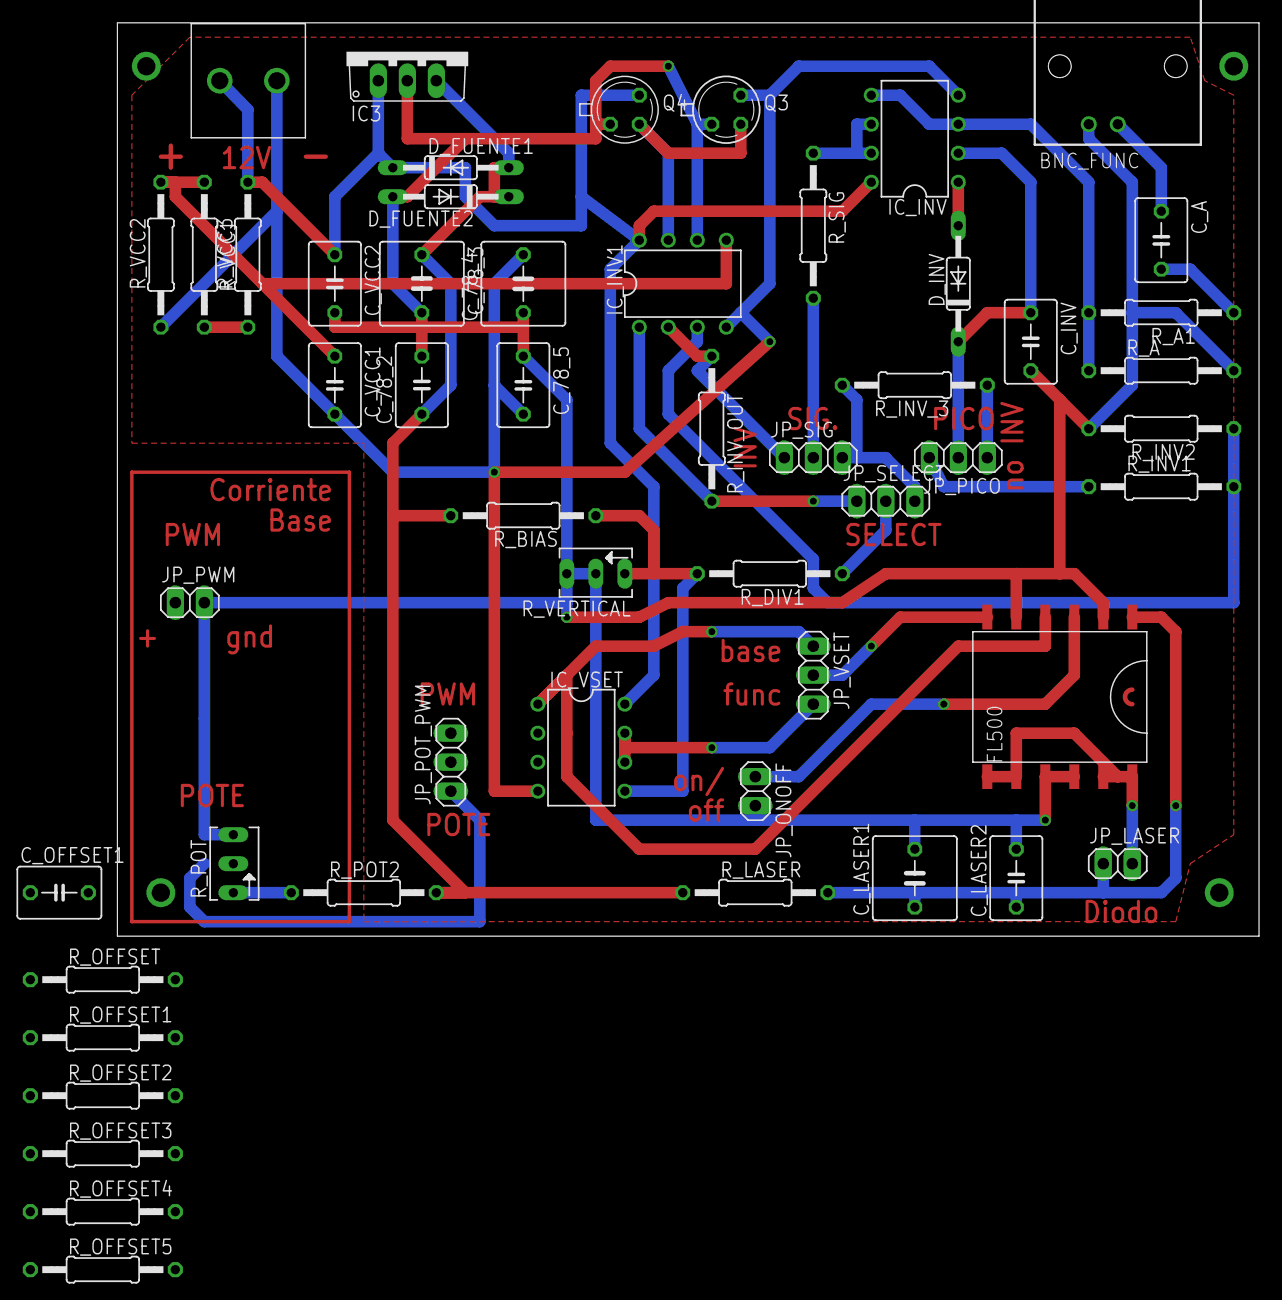
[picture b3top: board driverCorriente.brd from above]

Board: 2 copper layers, 100.0 x 80.0 mm, 53 parts (0 on the bottom side), 35 nets.
